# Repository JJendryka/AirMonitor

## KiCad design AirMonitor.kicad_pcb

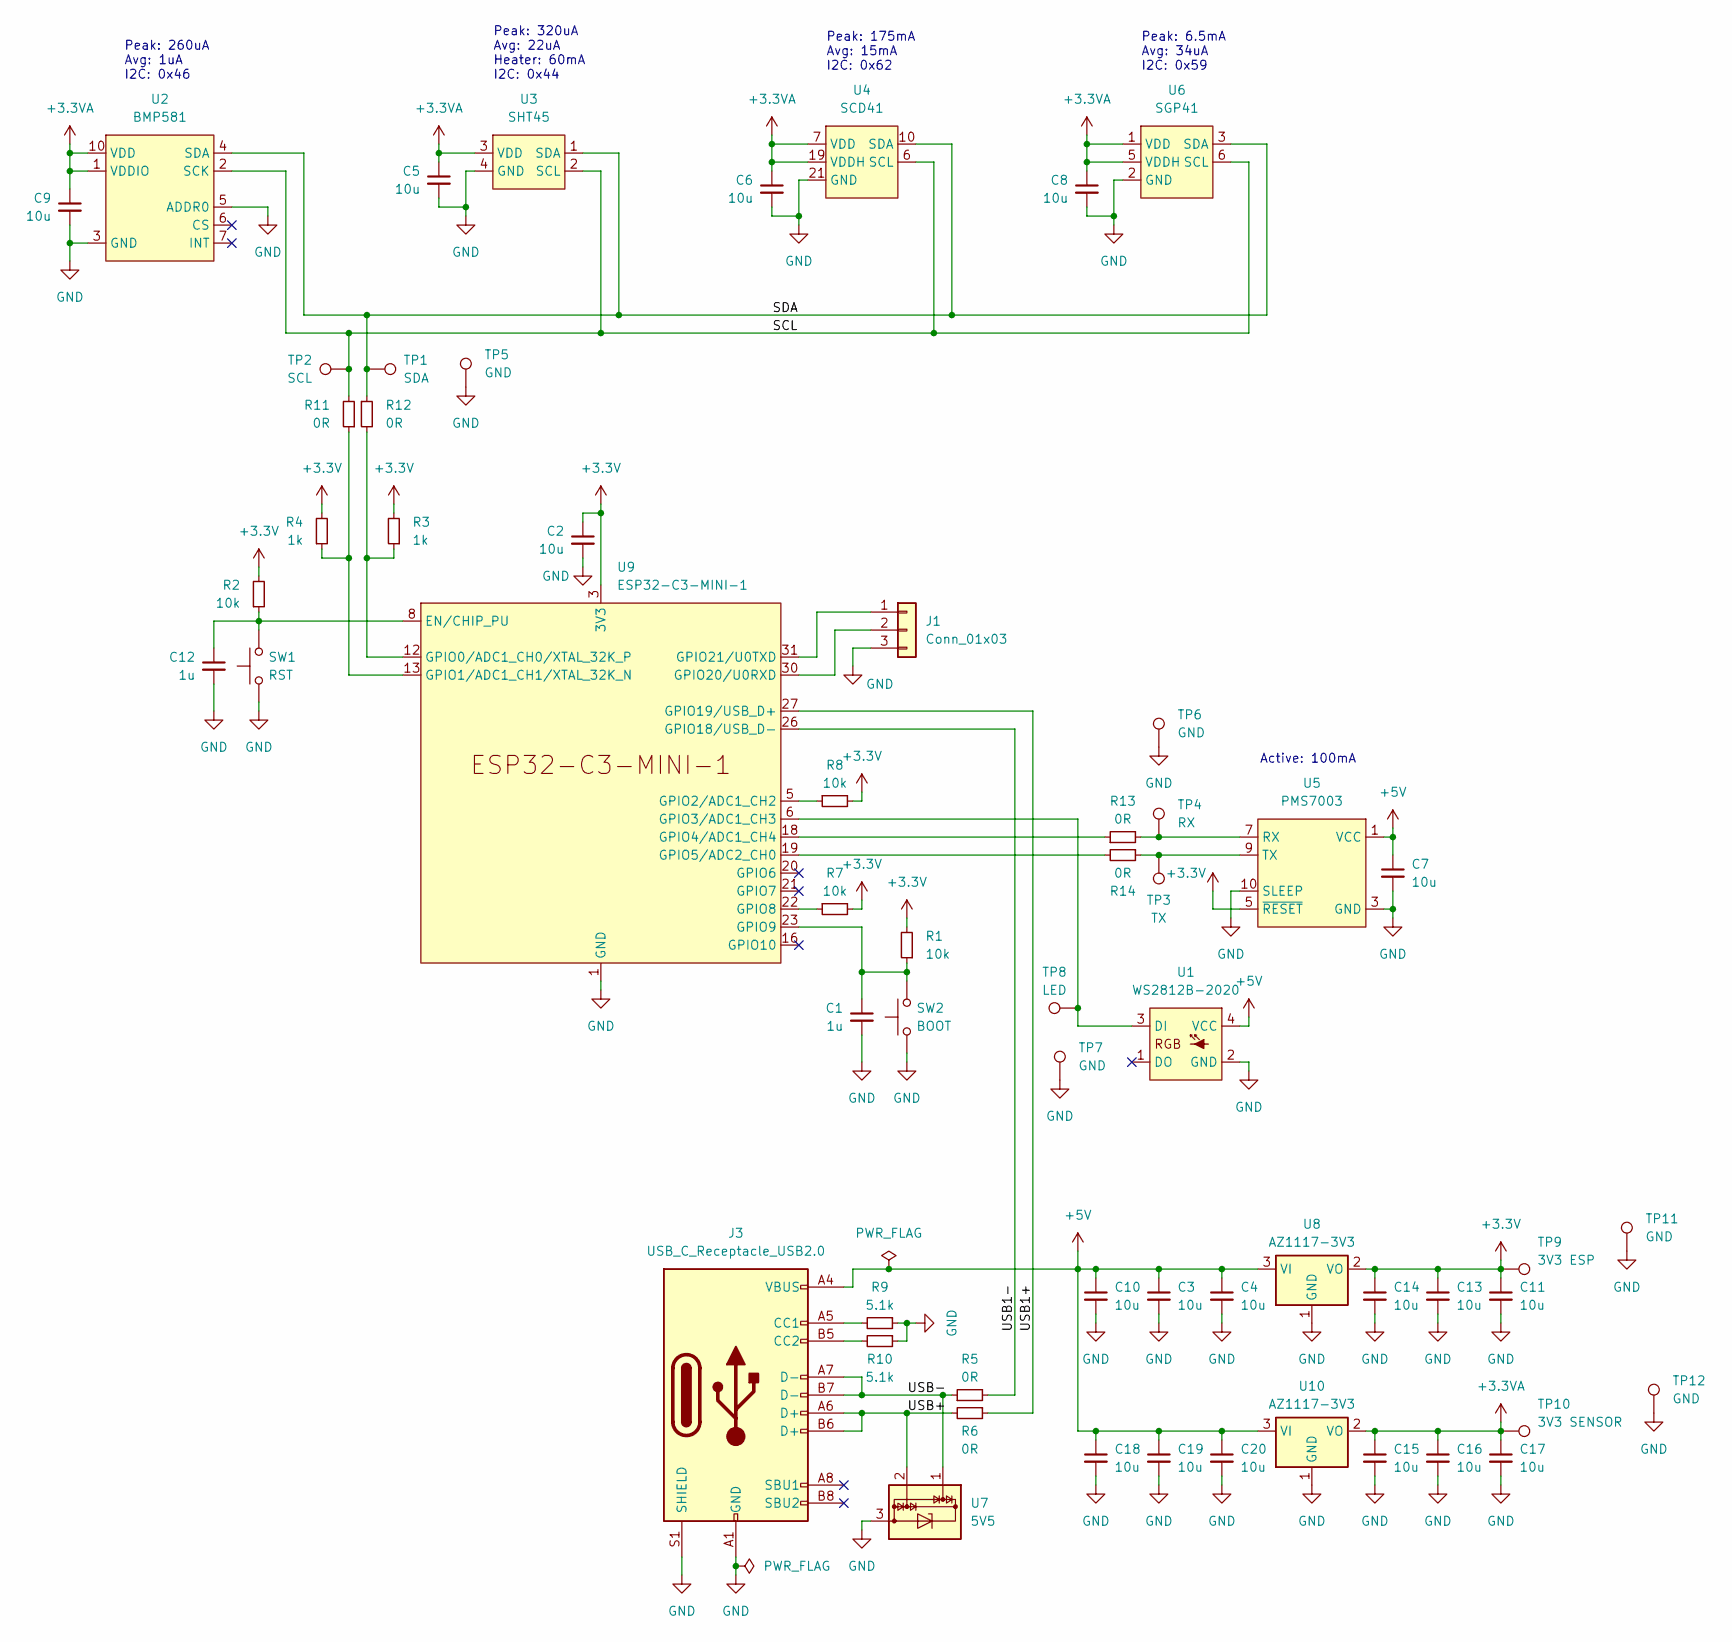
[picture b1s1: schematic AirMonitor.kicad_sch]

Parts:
C1, C12: 1u; C_0805_2012Metric
C2, C3, C4, C5, C6, C7, C8, C9, C10, C11, C13, C14, C15, C16, C17, C18, C19, C20: 10u; C_0805_2012Metric
J1: Conn_01x03; PinHeader_1x03_P2.54mm_Vertical_SMD_Pin1Left; MPN NO_MPN
J3: USB_C_Receptacle_USB2.0; USB4105-GF-A; MPN USB4105-GF-A-120; Mouser 640-USB4105-GF-A-120
R1, R2, R7, R8: 10k; R_0805_2012Metric
R3, R4: 1k; R_0805_2012Metric
R5, R6, R11, R12, R13, R14: 0R; R_0402_1005Metric_Pad0.72x0.64mm_HandSolder
R9, R10: 5.1k; R_0805_2012Metric
SW1: RST; SW_SPST_B3S-1000; MPN B3S-1000; Mouser 653-B3S-1000
SW2: BOOT; SW_SPST_B3S-1000; MPN B3S-1000; Mouser 653-B3S-1000
TP1: SDA; TestPoint_Pad_D1.0mm
TP2: SCL; TestPoint_Pad_D1.0mm
TP3: TX; TestPoint_Pad_D1.0mm
TP4: RX; TestPoint_Pad_D1.0mm
TP5, TP6, TP7, TP11, TP12: GND; TestPoint_Pad_D1.0mm
TP8: LED; TestPoint_Pad_D1.0mm
TP9: 3V3 ESP; TestPoint_Pad_D1.0mm
TP10: 3V3 SENSOR; TestPoint_Pad_D1.0mm
U1: WS2812B-2020; MPN 4684; Mouser 485-4684 - THIS IS A 10x PACK
U2: BMP581; MPN BMP581; Mouser 262-BMP581
U3: SHT45; SHT4x; MPN SHT45-AD1F-R2; Mouser 403-SHT45-AD1F-R2
U4: SCD41; SCD4x; MPN SCD41-D-R2; Mouser 403-SCD41-D-R2
U5: PMS7003; MPN PMS7003 + 20021311-00010T4LF; Mouser 649-221311-00010T4LF
U6: SGP41; DFN-6_EP_2.44x2.44_Pitch0.8mm; MPN SGP41-D-R4; Mouser 403-SGP41-D-R4
U7: 5V5; SOT-323_SC-70; MPN TPD2E2U06DCKR; Mouser 595-TPD2E2U06DCKR
U8, U10: AZ1117-3V3; SOT-223-3_TabPin2; MPN AZ1117IH-3.3TRG1; Mouser 621-AZ1117IH-3.3TRG1
U9: ESP32-C3-MINI-1; MPN ESP32-C3-MINI-1-N4; Mouser 356-ESP32-C3-MINI1N4

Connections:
+3.3V: C2.1, C11.1, C13.1, C14.1, R1.2, R2.2, R3.2, R4.2, R7.2, R8.2, TP9.1, U5.5 (~RESET), U8.2 (VO), U9.3 (3V3)
+3.3VA: C5.1, C6.1, C8.1, C9.1, C15.1, C16.1, C17.1, TP10.1, U2.1 (VDDIO), U2.10 (VDD), U3.3 (VDD), U4.7 (VDD), U4.19 (VDDH), U6.1 (VDD), U6.5 (VDDH), U10.2 (VO)
+5V: C3.1, C4.1, C7.1, C10.1, C18.1, C19.1, C20.1, J3.A4 (VBUS), J3.A9 (VBUS), J3.B4 (VBUS), J3.B9 (VBUS), U1.4 (VCC), U5.1 (VCC), U5.2 (VCC), U8.3 (VI), U10.3 (VI)
/SDA: R12.1, TP1.1, U2.4 (SDA), U3.1 (SDA), U4.10 (SDA), U6.3 (SDA)
/USB1+: R6.1, U9.27 (GPIO19/USB_D+)
/USB1-: R5.2, U9.26 (GPIO18/USB_D-)
/USB+: J3.A6 (D+), J3.B6 (D+), R6.2, U7.2
/USB-: J3.A7 (D-), J3.B7 (D-), R5.1, U7.1
unnamed: J1.1, U9.31 (GPIO21/U0TXD)
unnamed: J1.2, U9.30 (GPIO20/U0RXD)
unnamed: J3.A5 (CC1), R9.2
unnamed: J3.B5 (CC2), R10.2
unnamed: TP8.1, U1.3 (DI), U9.6 (GPIO3/ADC1_CH3)
unnamed: R13.2, TP4.1, U5.7 (RX)
unnamed: R14.1, TP3.1, U5.9 (TX)
unnamed: C12.1, R2.1, SW1.2, U9.8 (EN/CHIP_PU)
unnamed: R3.1, R12.2, U9.12 (GPIO0/ADC1_CH0/XTAL_32K_P)
unnamed: R4.1, R11.1, U9.13 (GPIO1/ADC1_CH1/XTAL_32K_N)
unnamed: R8.1, U9.5 (GPIO2/ADC1_CH2)
unnamed: R13.1, U9.18 (GPIO4/ADC1_CH4)
unnamed: R14.2, U9.19 (GPIO5/ADC2_CH0)
unnamed: R7.1, U9.22 (GPIO8)
unnamed: C1.1, R1.1, SW2.2, U9.23 (GPIO9)

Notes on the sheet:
Peak: 175mA Avg: 15mA I2C: 0x62
Peak: 6.5mA Avg: 34uA I2C: 0x59
Active: 100mA
Peak: 260uA Avg: 1uA I2C: 0x46
Peak: 320uA Avg: 22uA Heater: 60mA I2C: 0x44

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
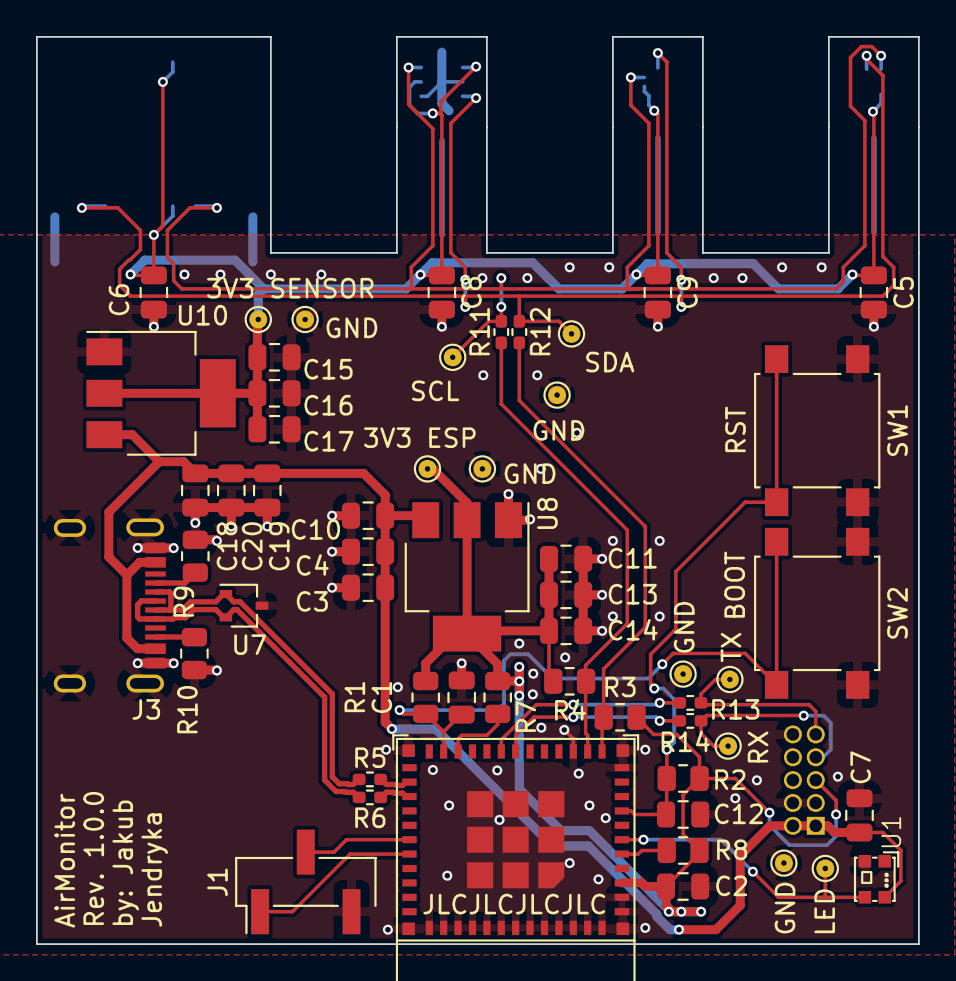
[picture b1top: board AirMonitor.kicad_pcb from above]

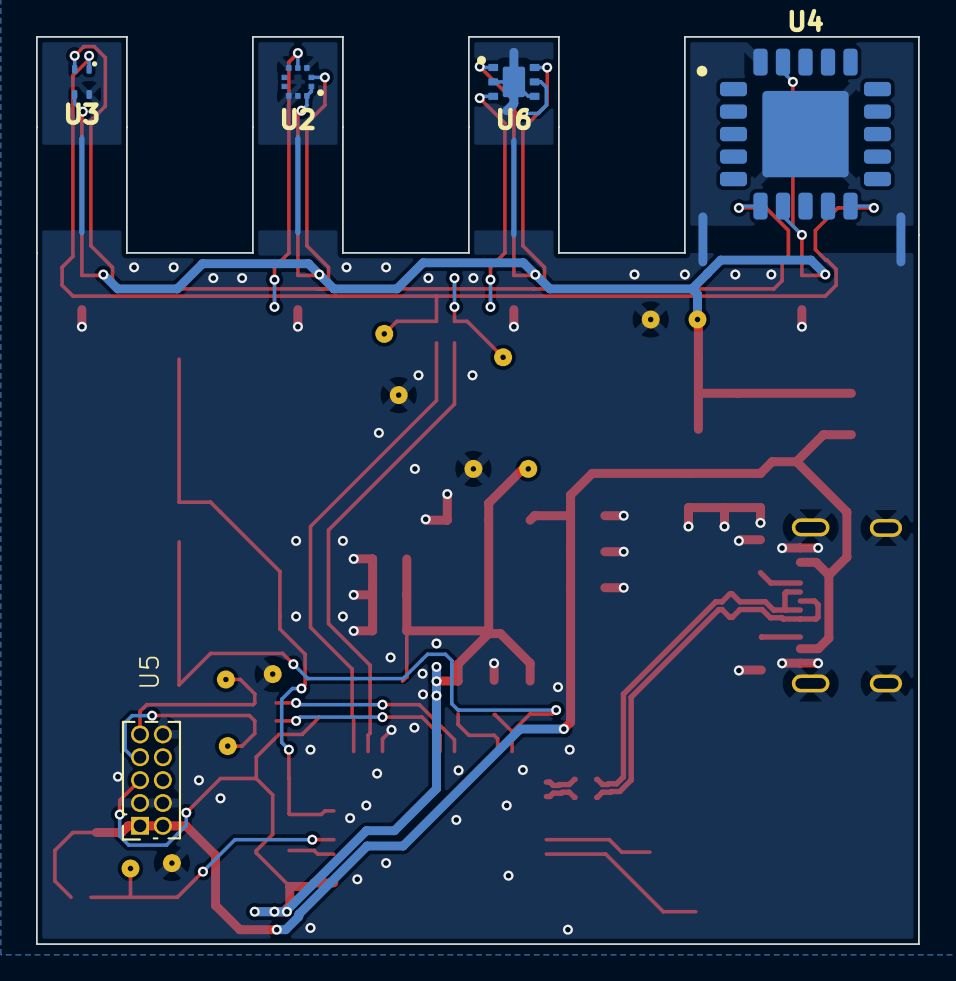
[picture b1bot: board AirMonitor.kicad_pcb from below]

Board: 2 copper layers, 49.0 x 50.4 mm, 60 parts (5 on the bottom side), 25 nets.

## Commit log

2023-12-08 Init repo
2023-12-09 Added gitignore
2023-12-09 Working revision
2023-12-09 Generated BOM
2023-12-09 Generated Gerbers
2023-12-09 Added JLCPCB mark location
